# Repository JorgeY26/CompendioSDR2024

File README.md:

# CompendioSDR2024
Se realiza una recopilación de todos los archivos desarrollados y utilizados en cada una de las actividades realizadas a lo largo del semestre ABR-AGO2024 en la materia de Radio Definida por Software de la Carrera de Ingeniería en Telecomunicaciones de la Universidad Técnica del Norte

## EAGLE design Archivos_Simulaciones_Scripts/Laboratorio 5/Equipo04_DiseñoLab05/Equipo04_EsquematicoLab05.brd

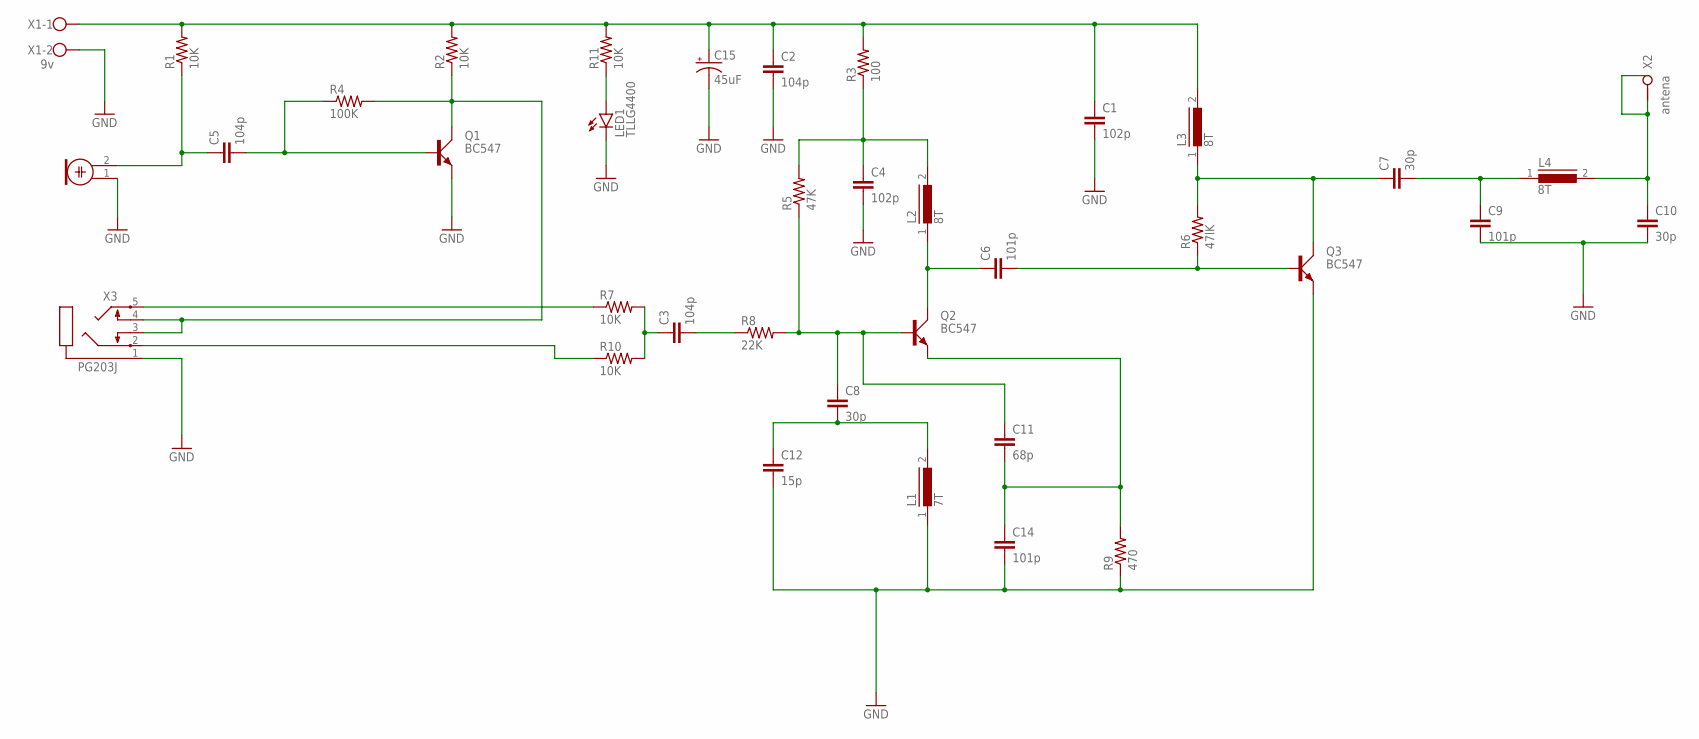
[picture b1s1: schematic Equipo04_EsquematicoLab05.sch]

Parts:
C1, C4: 102p; C050-024X044
C2, C3, C5: 104p; C050-024X044
C6, C9, C14: 101p; C050-024X044
C7, C8, C10: 30p; C050-024X044
C11: 68p; C050-024X044
C12: 15p; C050-024X044
C15: 45uF; E2-5
L1: 7T; A26GFC
L2, L3, L4: 8T; A26GFC
LED1: TLLG4400; LED3MM
M1: ELECTRET_MICROPHON-WM-62PC/62PK; WM-62PC/62PK
Q1, Q2, Q3: BC547; SOT54A
R1, R2, R7, R10, R11: 10K; 0309/10
R3: 100; 0309/10
R4: 100K; 0309/10
R5: 47K; 0309/10
R6: 47lK; 0309/10
R8: 22K; 0309/10
R9: 470; 0309/10
X1: 9v; W237-102
X2: antena; W236-1
X3: PG203J

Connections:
GND: C1.2, C2.2, C4.2, C9.2, C10.2, C12.2, C14.2, C15.-, L1.1, LED1.K (C), M1.1, Q1.E, Q3.E, R9.1, X1.2, X3.1
unnamed: C4.1, L2.2, R3.1, R5.2
unnamed: C1.1, C2.1, C15.+, L3.2, R1.2, R2.2, R3.2, R11.2, X1.1
unnamed: C5.1, M1.2, R1.1
unnamed: C5.2, Q1.B, R4.1
unnamed: Q1.C, R2.1, R4.2, X3.3, X3.4
unnamed: LED1.A, R11.1
unnamed: R7.1, X3.5
unnamed: R10.1, X3.2
unnamed: C3.1, R7.2, R10.2
unnamed: C3.2, R8.1
unnamed: C6.1, L2.1, Q2.C
unnamed: C8.1, C11.1, Q2.B, R5.1, R8.2
unnamed: C8.2, C12.1, L1.2
unnamed: C7.2, C9.1, L4.1
unnamed: C11.2, C14.1, Q2.E, R9.2
unnamed: C6.2, Q3.B, R6.1
unnamed: C7.1, L3.1, Q3.C, R6.2
unnamed: C10.1, L4.2, X2.1 (KL1)

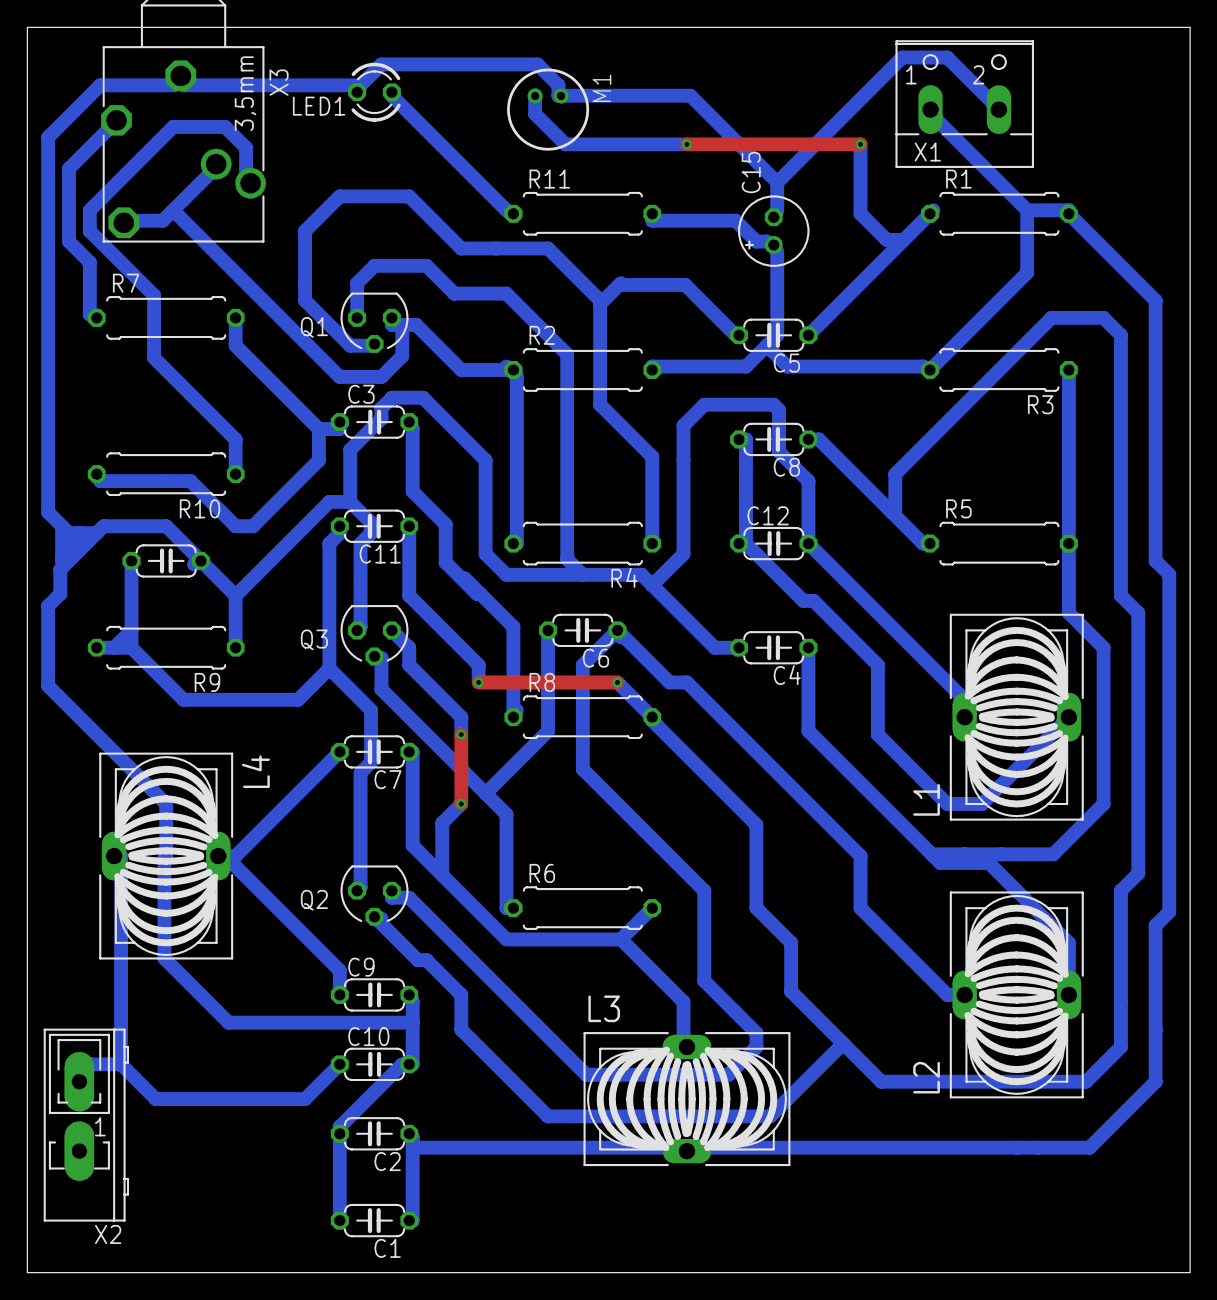
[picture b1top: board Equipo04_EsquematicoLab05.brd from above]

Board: 2 copper layers, 85.1 x 91.1 mm, 37 parts (0 on the bottom side), 19 nets.
